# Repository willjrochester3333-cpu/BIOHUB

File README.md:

# Biohub — Cell Tracking During Development

Baseline solution for the Kaggle "Biohub - Cell Tracking During Development"
competition: detect zebrafish cells in 3D+time microscopy volumes, link them
across frames, recover cell divisions, and reconstruct lineages.

## Approach

No trained model or ground truth is required — this is a classical
computer-vision baseline meant to run standalone in a Kaggle Notebook with
internet access disabled, and to serve as a starting point to improve on.

1. **Detection** (`src/detection.py`): anisotropic Gaussian smoothing (voxel
   sigma derived from the physical scale, since z spacing is ~4x coarser
   than xy) → Otsu/relative intensity threshold → local maxima spaced by a
   physical radius (not voxel count) → marker-controlled watershed →
   intensity-weighted centroid per region.
2. **Linking** (`src/tracking.py`): frame-to-frame 1-1 assignment via the
   Hungarian algorithm (`scipy.optimize.linear_sum_assignment`) on
   physically-scaled centroid distance. The cost matrix is padded with
   dummy rows/columns (cost = distance threshold) so cells can appear,
   disappear, or go unmatched instead of being forced into a bad pairing.
3. **Division recovery**: any cell left unmatched by the 1-1 step is
   attached to its nearest neighbor in the previous frame (within a looser
   distance gate). If that parent already has an edge, it now has two —
   a division.
4. **Submission** (`src/submission.py`): formats nodes and edges into the
   required `submission.csv` schema.

## Layout

```
main.py          single-file version: everything inlined into one main()
notebook/kaggle_submission.ipynb   same thing, split across notebook cells
src/
  detection.py   3D blob detection for one timepoint volume
  tracking.py    frame-to-frame linking + division recovery
  data.py        zarr access (OME-NGFF multiscale, bare 4D/5D array, or legacy per-timepoint group)
  submission.py  submission.csv formatting
  pipeline.py    end-to-end driver (discovers test datasets, writes submission.csv)
notebook/
  kaggle_submission.ipynb   self-contained notebook to upload directly to Kaggle
tests/
  test_synthetic.py         smoke test on a synthetic moving+dividing cell
```

## Running

```bash
pip install -r requirements.txt
python3 -m pytest tests/ -v          # synthetic smoke test (no real data needed)
python3 -m src.pipeline              # edit TEST_DIR/OUTPUT_PATH at the bottom of pipeline.py

# or the single-file version (test_dir auto-detects a *.zarr folder under
# /kaggle/input if not given explicitly):
python3 main.py --output /kaggle/working/submission.csv
```

For the actual Kaggle submission, upload `notebook/kaggle_submission.ipynb`
as a Code Competition notebook, or paste the contents of `main.py` into a
single notebook cell and call:

```python
submission = main(output_path="/kaggle/working/submission.csv")
```

Both are fully self-contained (no dependency on this repo's `src/` package)
and produce byte-identical output — `main.py` is the same detect/link/divide/
submit logic as `src/`, just inlined into one `main()` function for people
who'd rather copy-paste one block than manage multiple files.
`discover_test_dir()` walks `/kaggle/input` looking for a folder that
directly contains `*.zarr` datasets (preferring one named `test`), since the
competition slug in the mounted path isn't known ahead of time — pass
`test_dir=...` explicitly to override.

`ZarrTimeSeries` (in `src/data.py`, `main.py`, and the notebook's data-access
cell) auto-detects the on-disk layout: OME-NGFF multiscale groups (using the
`.zattrs` `multiscales`/`axes` metadata to pick the finest resolution level
and the right time/channel axes), a bare `(T, Z, Y, X)` or `(T, C, Z, Y, X)`
array, or the legacy convention of one 3D array per timepoint keyed `"0"`,
`"1"`, .... If a real dataset doesn't fit any of these, run `inspect_zarr(path)`
(exported alongside `ZarrTimeSeries`) on it to print its structure and adjust
`ZarrTimeSeries._resolve` accordingly.

**Before relying on this for a leaderboard score**, tune `DetectionParams` /
`TrackingParams` against a few training volumes with known ground truth —
thresholds and distance gates are density- and noise-dependent.

## Where to improve

- Swap the classical watershed detector for a learned 3D segmentation model
  (e.g. StarDist3D or a U-Net), especially for dense/irregular cell
  populations where intensity-based watershed under- or over-segments.
- Add appearance features (intensity, size) to the linking cost, not just
  distance.
- Bridge missed detections with skip-frame linking (link t → t+2 when a
  cell has no match at t+1).
- Tighten division heuristics (`recover_divisions`) to cut false positives
  from detection noise — e.g. require daughter size/intensity symmetry.

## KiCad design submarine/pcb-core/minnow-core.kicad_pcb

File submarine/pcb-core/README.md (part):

# Minnow Core: the all-in-one board

This is the "buy almost nothing" version of the Minnow electronics. JLCPCB solders **every part** for you:
the ESP32, the USB programming port, the magnet on/off switch, the 5 V and 3.3 V supplies, the compass, the
hull leak/pressure sensor, the LoRa radio and all the connectors. There is nothing to solder on the board.

**The whole sub can be built without soldering.** Everything connects to the board with plugs (battery, camera,
antenna, USB) or **screw terminals** (strip a wire, push it in, tighten the screw), and the few wire-to-wire joins
use lever connectors and heat-shrink crimp splices. See [Building it without soldering](#building-it-without-soldering)
and the [solder-free shopping list](../bom/shopping_list.md).

**Order two.** One goes in the sub. The other is your **shore radio**: plug it into a laptop with a USB-C cable
and it talks to the sub over LoRa. You don't need any other radio, USB adapter or base station.

| Top | Bottom |
|---|---|
|  |  |

It has the same outline (150 x 60 mm) and mounting holes as the rev 1 carrier board in [`../pcb`](../pcb), so it
fits the same sled in the hull, and the mechanical design does not change. Two small differences: the magnet mark
moves to the side of the hull (see below), and because the board is lighter than the rev 1 board with its DevKit,
radio and compass bracket, the sub needs about 617 g of lead instead of 579 g (the 1 kg bag covers it). Build the
Blender model with `python3.11 build_sub.py --core` to see it and get the exact trim.

## What is on the board

| Job | Part on the board | Replaces (rev 1) |
|---|---|---|
| Brain | ESP32-WROOM-32E-N8 module (Wi-Fi for the camera, Bluetooth) | ESP32-S3 DevKit |
| Programming / shore link | USB-C + CH340C USB serial, auto-reset, BOOT and RESET buttons | DevKit USB, CH340 adapter |
| Compass / IMU | Bosch BNO055 9-axis sensor with its own sensor fusion, plus a 32.768 kHz crystal | BNO085 breakout |
| Hull monitor | Bosch BME280 (pressure for the vacuum test, humidity for early leak warning) | BME280 breakout |
| Radio | Ai-Thinker Ra-01H LoRa (SX1276, 868 MHz) with a U.FL antenna socket | 2 x E220 modules + USB adapter |
| On/off | Honeywell SM351LT magnet sensor at the board edge + always-on 3 uA supply: hold a magnet on the hull | reed switch on a lead |
| Power | 15 A fuse, two 40 A P-MOSFET switch, 18 V surge clamp, 5 V / 3 A buck (TPS54302), 3.3 V LDO | same idea, through-hole parts |
| Camera power | USB-A socket for the GoPro's own cable, switched by the ESP32, 1.5 A resettable fuse | USB-A breakout on a lead |
| Thrusters | Screw terminals for the signal wires of four single ESCs (DShot), 1 kΩ protection on every signal | JST-PH 7-pin to a 4-in-1 ESC |
| Outputs | Strobe and spare (lights / pump) low-side switches, up to 3 A each | same |
| Wiring | Screw terminals for the GPS, depth sensor, 2 leak probes, strobe and AUX (each screw labelled on the board); XT60 battery in, XT30 out to the ESCs | JST sockets |

```mermaid
flowchart LR
    BAT[3S battery XT60] --> F[15 A fuse] --> SW[2 x P-MOSFET switch]
    MAG((magnet)) -.-> HALL[SM351LT magnet sensor<br/>always on, 3 uA] --> SW
    SW --> ESCP[XT30 to the ESCs]
    SW --> BUCK[5 V / 3 A buck] --> LDO[3.3 V LDO]
    USB[USB-C] --> CH[CH340C] <--> MCU
    USB --> LDO
    LDO --> MCU[ESP32-WROOM-32E]
    MCU -- PWR_HOLD --> SW
    MCU -- I2C --> IMU[BNO055 compass] & BME[BME280 hull] & DEP[depth socket]
    MCU -- SPI --> LORA[Ra-01H LoRa] --> ANT[U.FL antenna]
    MCU -- UART --> GPS[GPS socket]
    MCU -- DShot x4 --> ESCS[ESC signal screw terminals]
    MCU --> CAM[camera USB-A 5 V] & OUT[strobe / AUX outputs]
    MCU -. Wi-Fi .-> GOPRO[GoPro]
```

## What you still need to buy

The board can't hold the things that must be outside the hull, at the top of the mast or under the
battery. These are the electronics you still buy (the mechanical parts are unchanged, see the
[shopping list](../bom/shopping_list.md)):

| Qty | Item | Why it can't be on the board | Link |
|---:|---|---|---|
| 1 | **GPS** Beitian BN-220 | needs to see the sky from the mast | [Amazon UK](https://www.amazon.co.uk/s?k=Beitian+BN-220+GPS) |
| 1 | **Depth sensor** MS5837-30BA module with the pins already fitted (+ female-to-male jumper wires) | must touch the water, through the rear cap | [Amazon UK](https://www.amazon.co.uk/s?k=MS5837-30BA) · [eBay UK](https://www.ebay.co.uk/sch/i.html?_nkw=MS5837-30BA) |
| 4 | **Single ESCs** (BLHeli_S / Bluejay, 20–30 A, DShot) **with their wires already attached** | they carry the motor current | [Amazon UK](https://www.amazon.co.uk/s?k=BLHeli_S+30A+ESC+2-4S+4+pack) |
| 4 | **Motors** A2212 1000KV | they are the thrusters | [Amazon UK](https://www.amazon.co.uk/s?k=A2212+1000KV+brushless+motor) |
| 1 | **Battery** 3S 18650 pack with BMS and XT60 | (+ charger) | [Amazon UK](https://www.amazon.co.uk/s?k=3S+18650+battery+pack+BMS+11.1V+XT60) |
| 1 | **GoPro** HERO5/6/7 Black + 64 GB card + short USB-A to USB-C cable | the 4K camera | [eBay UK](https://www.ebay.co.uk/sch/i.html?_nkw=GoPro+HERO5+Black) |
| 2 | **868 MHz antennas** with a U.FL plug: one with a ~30 cm cable for the mast, one for the shore board | the antenna must be above water | [Amazon UK](https://www.amazon.co.uk/s?k=868MHz+antenna+IPEX+u.fl) |
| 1 | **Small magnet** (6–10 mm neodymium disc) | it is the on/off key | [Amazon UK](https://www.amazon.co.uk/s?k=N52+neodymium+magnet+10mm+x+5mm) |
| 1 | **Wiring kit:** heat-shrink crimp splices (22–16 AWG), 2 Wago 221-415 lever connectors, an XT30 male lead | joins without solder | [splices](https://www.amazon.co.uk/s?k=heat+shrink+butt+connectors+waterproof+22-16+AWG) · [Wago](https://www.amazon.co.uk/s?k=Wago+221-415) · [XT30](https://www.amazon.co.uk/s?k=XT30+male+pigtail+14AWG) |
| 1 | Strobe: a **12 V white LED with wires attached** (built-in resistor) | it sits in the mast | [Amazon UK](https://www.amazon.co.uk/s?k=12V+white+LED+pre+wired) |

Compared with the rev 1 board this removes the ESP32 DevKit, the BNO085, the BME280, two E220 radios, the USB
serial adapter, the reed switch, the USB-A breakout, the 38 lines of loose PCB parts and all of the soldering.
The full list for the whole sub, with links, is the [solder-free shopping list](../bom/shopping_list.md).

## Cost

Rough numbers from JLCPCB's parts library on 2026-11-11 (check the live quote, prices move):

| | USD |
|---|---:|
| Parts for two boards (BNO055 $9, BME280 $8, Ra-01H $6.50 and ESP32 $4.60 each are most of it) | ~80 |
| "Extended part" loading fee, 19 kinds of part x $3 | ~57 |
| Assembly setup, stencil, machine soldering of the through-hole connectors and screw terminals | ~35 |
| 5 bare PCBs (2 get assembled, 3 spare) | ~10 |
| Shipping to the UK | ~15–30 |
| **Total before VAT** | **~200–215** |
| **With UK VAT (JLCPCB charges it at checkout)** | **about £190–205** |

The rev 1 parts it replaces (DevKit, PCB and its parts, BNO085, BME280, two E220 radios, USB adapter, reed switch,
USB-A breakout, antenna pigtails) come to about £80, so the Core board costs roughly £110–125 more. In exchange
there is no soldering, the board is assembled and inspected by machine, and you get a second board as the
shore station.

**Ways to bring it down:**
* Leave out the hull monitor U10 (BME280): mark it "do not place" on the BOM page. Saves about £17. The leak
  probes still work, and you lose the automatic vacuum test.
* (Not for a solder-free build: choosing **Economic** assembly and soldering the through-hole connectors and
  screw terminals yourself saves roughly £20–25.)

## Ordering from JLCPCB, step by step

1. Go to [jlcpcb.com/quote](https://cart.jlcpcb.com/quote) and upload
   [`output/minnow-core-gerbers.zip`](output/minnow-core-gerbers.zip). It reads 150 x 60 mm, 2 layers.
2. PCB options: thickness 1.6 mm, quantity 5, any colour, surface finish HASL lead-free (or ENIG). Leave
   everything else at the default.
3. Turn on **PCB Assembly**: **Standard** PCBA (needed for the three through-hole connectors), assemble the
   **top side**, PCBA quantity **2**. Leave "Confirm parts placement" on.
4. Upload [`output/minnow-core-jlcpcb-bom.csv`](output/minnow-core-jlcpcb-bom.csv) as the BOM and
   [`output/minnow-core-jlcpcb-cpl.csv`](output/minnow-core-jlcpcb-cpl.csv) as the CPL (pick-and-place) file.
5. On the parts page every line should match a part (they all carry an LCSC number). If a part shows
   "out of stock", pick the suggested alternative with the same package and value.
6. **Check the placement preview.** The CPL already includes the usual JLCPCB rotation fixes, but look at every
   chip: the dot or notch on the part must match the dot on the footprint, the electrolytic capacitors'
   stripe must be on the minus side, and the USB and XT connectors and the screw terminals (wire openings) must face
   the board edge. Rotate any that
   are wrong right there on the page. JLCPCB's engineers check it again before they build.
7. Pay. Boards usually arrive in about 1–2 weeks.

## Connectors

| Ref | Silkscreen | Pins (1 → n) | Goes to |
|---|---|---|---|
| J1 | BATTERY | 1 −, 2 + (XT60 male) | battery (XT60 female) |
| J2 | ESC POWER | 1 −, 2 + (XT30 female) | XT30 lead → two Wago lever connectors → the four ESC power leads |
| J10 + J17 | G M1 M2 / M3 M4 (screws, starboard edge) | ground, then the four DShot signals | the ESCs' signal wires (and one ground) |
| J5 + J15 | 5V G / TX RX (screws, starboard edge) | +5 V, GND, TX from the GPS, RX to the GPS | BN-220 GPS |
| J6 + J16 | 3V3 G / SDA SCL (screws, port edge) | +3.3 V, GND, I2C | MS5837-30BA depth sensor (address 0x76) |
| J8 / J9 | LF G / LR G (screws, port edge) | leak sense, GND | leak probes: two bare wire ends each, at the lowest point of the hull |
| J11 | S+ S- (screws, port edge) | +battery, switched − | 12 V strobe LED in the mast |
| J12 | A+ A- (screws, port edge) | +battery, switched − (up to 3 A, flyback diode fitted) | lights or a pump |
| J13 | CAMERA 5V | USB-A, 5 V switched, 1.5 A fuse | GoPro (its own USB cable) |
| J3 | USB | USB-C | laptop: programming, serial monitor, shore station |
| J4 | LORA ANT | U.FL | 868 MHz antenna |

**Screw terminals:** 3.5 mm pitch, they take wires from 28 AWG (thin GPS wires) to 16 AWG. Strip 5 mm, twist the
strands, push the wire in fully and tighten the screw with a 2.5 mm screwdriver. The label next to each screw on the
board says what goes there. Every ESC signal has a 1 kΩ resistor, so a wire in the wrong screw will not damage
the ESP32.

## Building it without soldering

| Join | How | Parts |
|---|---|---|
| Battery → board | XT60 plug | already on the battery |
| Board → 4 ESCs (power) | XT30 lead into ESC POWER; its red wire and the four ESC red wires go into one Wago 221-415, the black wires into the other | XT30 male lead, 2 Wago 221-415 |
| ESC signal wires → board | Screw terminals M1–M4, plus one ESC ground wire into G. If an ESC also has a red "BEC" wire, leave it unconnected and cover the end with heat-shrink | — |
| ESC motor wires → thruster cables (inside the hull) | Heat-shrink crimp butt splices: crimp, then shrink | 12 splices |
| Thruster cables → motors (in the water) | The same splices; the glue inside seals them. Add a second layer of adhesive heat-shrink over each | 12 splices |
| GPS → board | Cut the plug off the free end of its cable, strip the 4 wires, screw them in | — |
| Depth sensor → board | Female-to-male jumper wires onto its pins, the pin ends into the screw terminals | 4 jumper wires |
| Strobe | A 12 V LED with wires attached, straight into S+ / S- | — |
| Leak probes | Two stripped wire ends each, into LF / G and LR / G | thruster cable offcut |
| Camera, antennas, laptop | USB-A, U.FL and USB-C plugs | — |

Tools: a ratchet crimper for insulated terminals, a wire stripper, a heat gun (or a lighter) and a small
screwdriver. The 3D-printed parts need no heat-set inserts either: screws cut their own thread, and the nose ring
and tail cone use glued studs and nuts (see [the mechanical guide](../docs/01-mechanical.md#16-frame-fairings-and-fasteners)),
so no soldering iron or hot tip is used anywhere in the build.

## Switching it on and off: the magnet

The SM351LT magnet sensor (U2) sits right at the port (left) edge of the board, next to the white arrow
marked MAGNET on the silkscreen. In the hull that point is **on the left side of the hull, level with the
middle of the hull, 53 mm behind the centre of the middle clamp**. Put a sticker or paint mark there.

* **On:** hold the magnet against the mark for a second. The sensor needs only about 1 mT, which a 6–10 mm
  neodymium disc gives through the 4.3 mm pipe wall with plenty to spare. The green 5 V LED and the red status
  LED come on, and the firmware takes over the power switch.
* **Off:** hold the magnet there for 3 seconds. The strobe flashes, you take the magnet away, and it turns off.
* If it doesn't react, turn the magnet 90 degrees. This kind of sensor (magnetoresistive) responds to a field
  along the board, so a magnet held flat against the hull side is the right way.
* Off, the board draws about 3 µA (a 3 Ah pack would take decades to drain), but still disconnect the battery for
  storage and charge it outside the hull.

## ESP32 pin map

| GPIO | Signal | Notes |
|---:|---|---|
| 0 | `ESP_IO0` | BOOT button / auto-program |
| 1 | `ESP_TXD` | USB serial (CH340C) |
| 2 | `LED_STAT` | red status LED |
| 3 | `ESP_RXD` | USB serial (CH340C) |
| 4 | `LORA_DIO0` | LoRa interrupt |
| 5 | `LORA_NSS` | LoRa chip select |
| 12 | `AUX_EN` | AUX output (lights / pump) |
| 13 | `CAM_EN` | camera 5 V on |
| 14 | `STROBE_EN` | strobe output |
| 15 | `MAG_SENSE` | magnet sensor (low = magnet) |
| 16 | `GPS_TX` | UART2 RX <- GPS TX |
| 17 | `GPS_RX` | UART2 TX -> GPS RX |
| 18 | `LORA_SCK` | SPI |
| 19 | `LORA_MISO` | SPI |
| 21 | `SDA` | I2C |
| 22 | `SCL` | I2C |
| 23 | `LORA_MOSI` | SPI |
| 25 | `ESC_M2` | DShot motor 2 |
| 26 | `ESC_M3` | DShot motor 3 |
| 27 | `ESC_M4` | DShot motor 4 |
| 32 | `PWR_HOLD` | keeps the power switch on |
| 33 | `ESC_M1` | DShot motor 1 |
| 34 | `LEAK_F` | leak probe front (ADC1) |
| 35 | `LEAK_R` | leak probe rear (ADC1) |
| 36 | `VBAT_SENSE` | battery voltage x 22/122 (ADC1) |
| 39 | `ESC_CURR_F` | ESC current sensor (ADC1) |

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
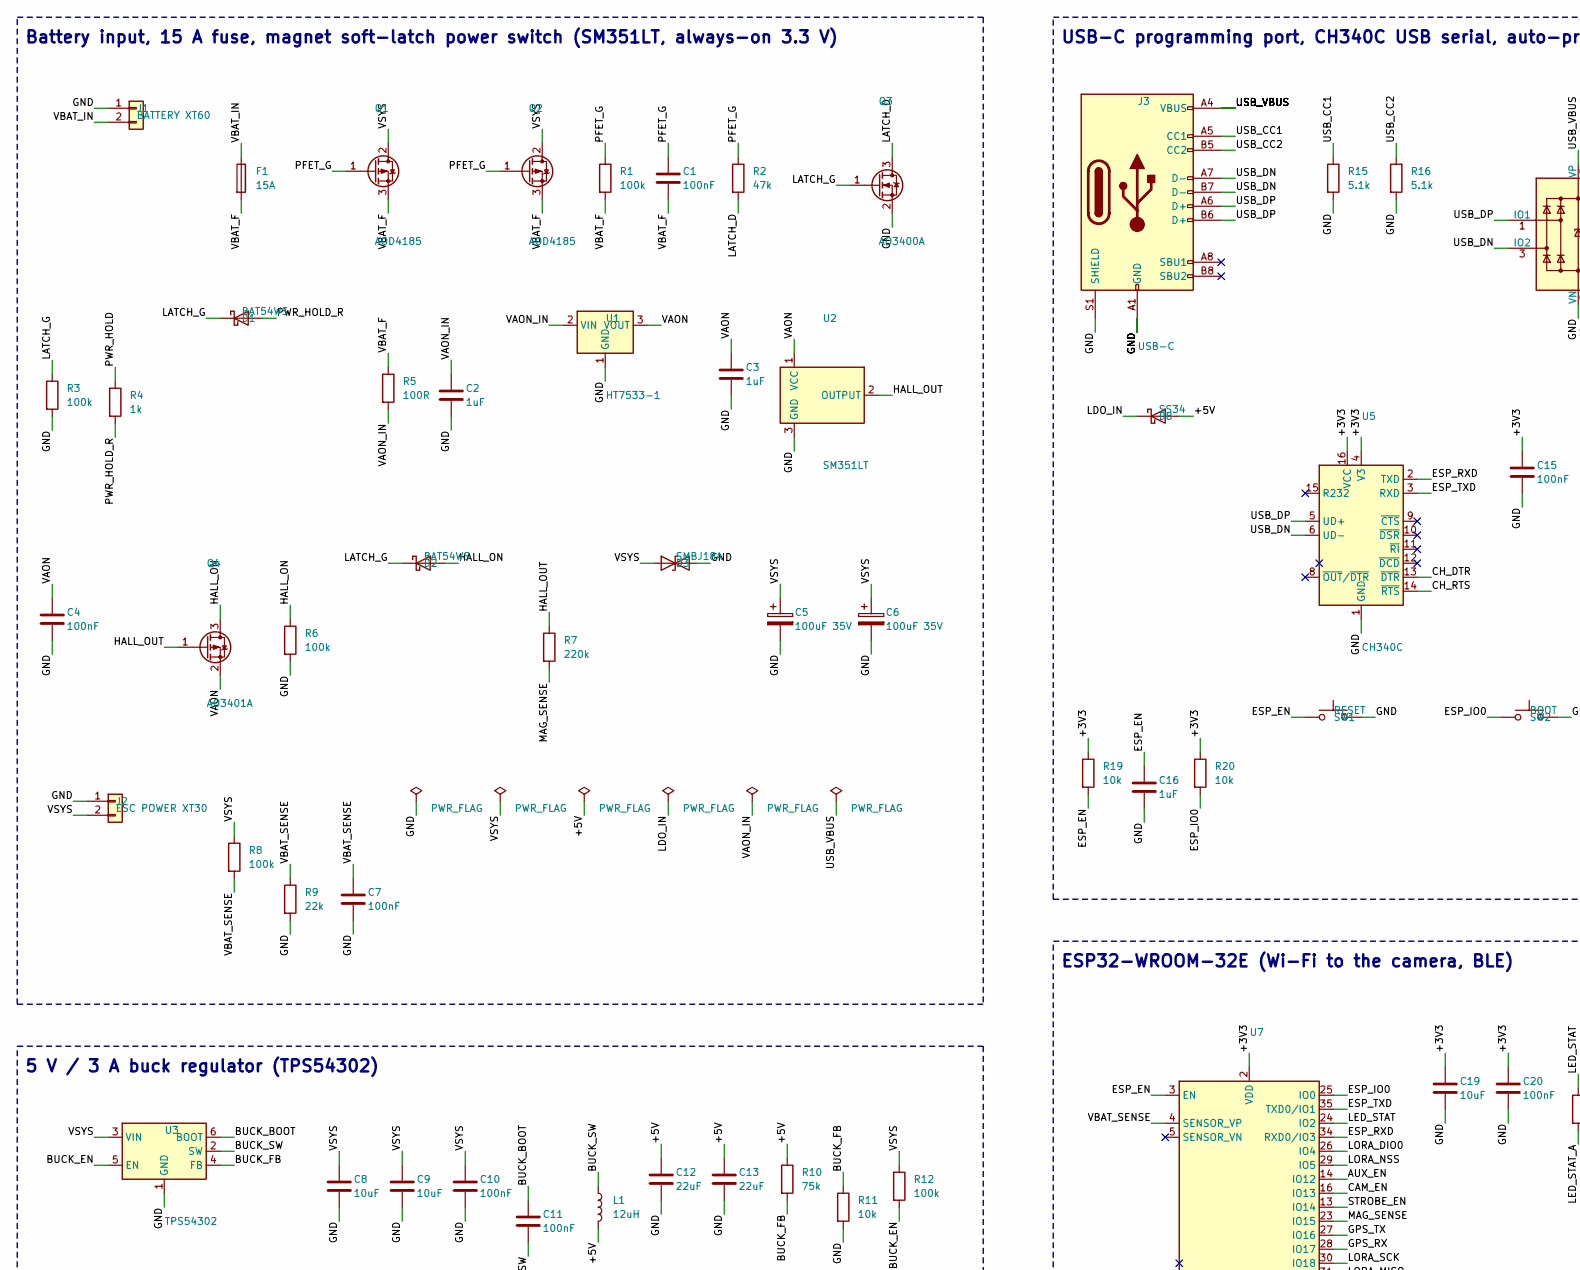
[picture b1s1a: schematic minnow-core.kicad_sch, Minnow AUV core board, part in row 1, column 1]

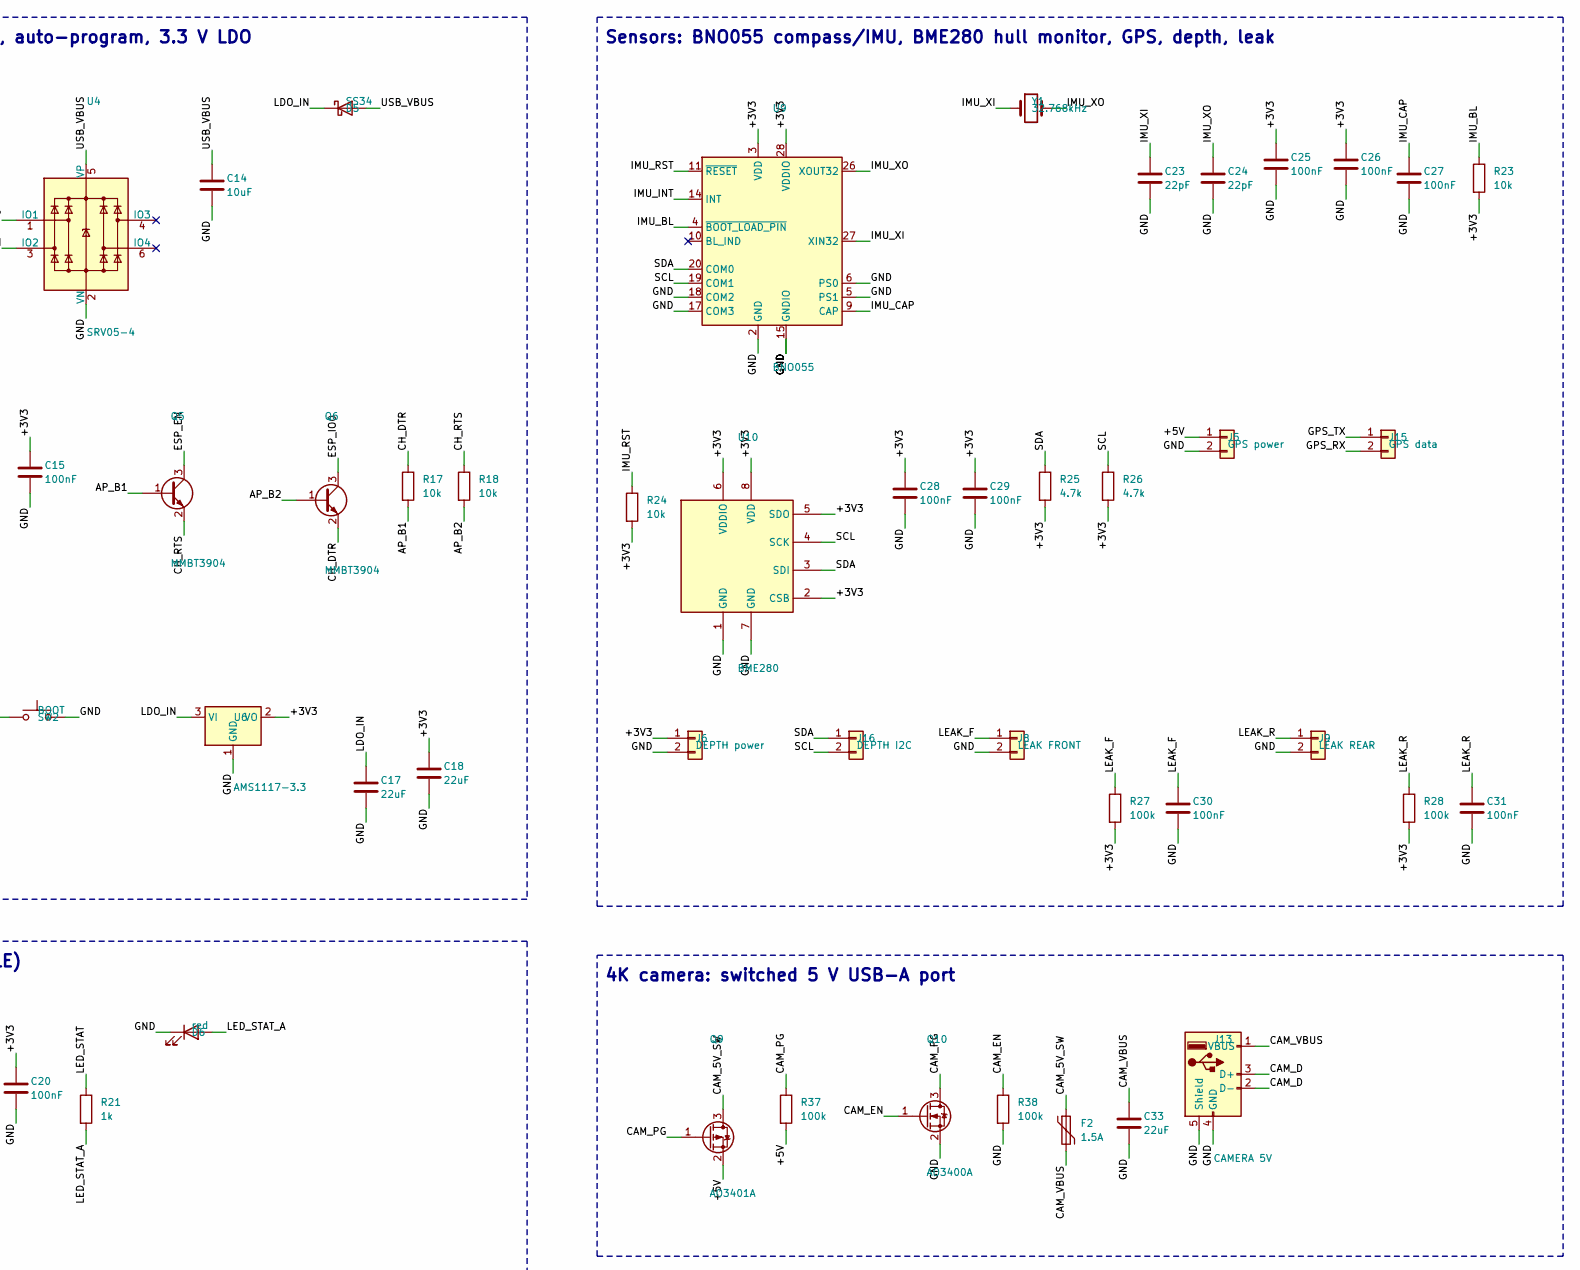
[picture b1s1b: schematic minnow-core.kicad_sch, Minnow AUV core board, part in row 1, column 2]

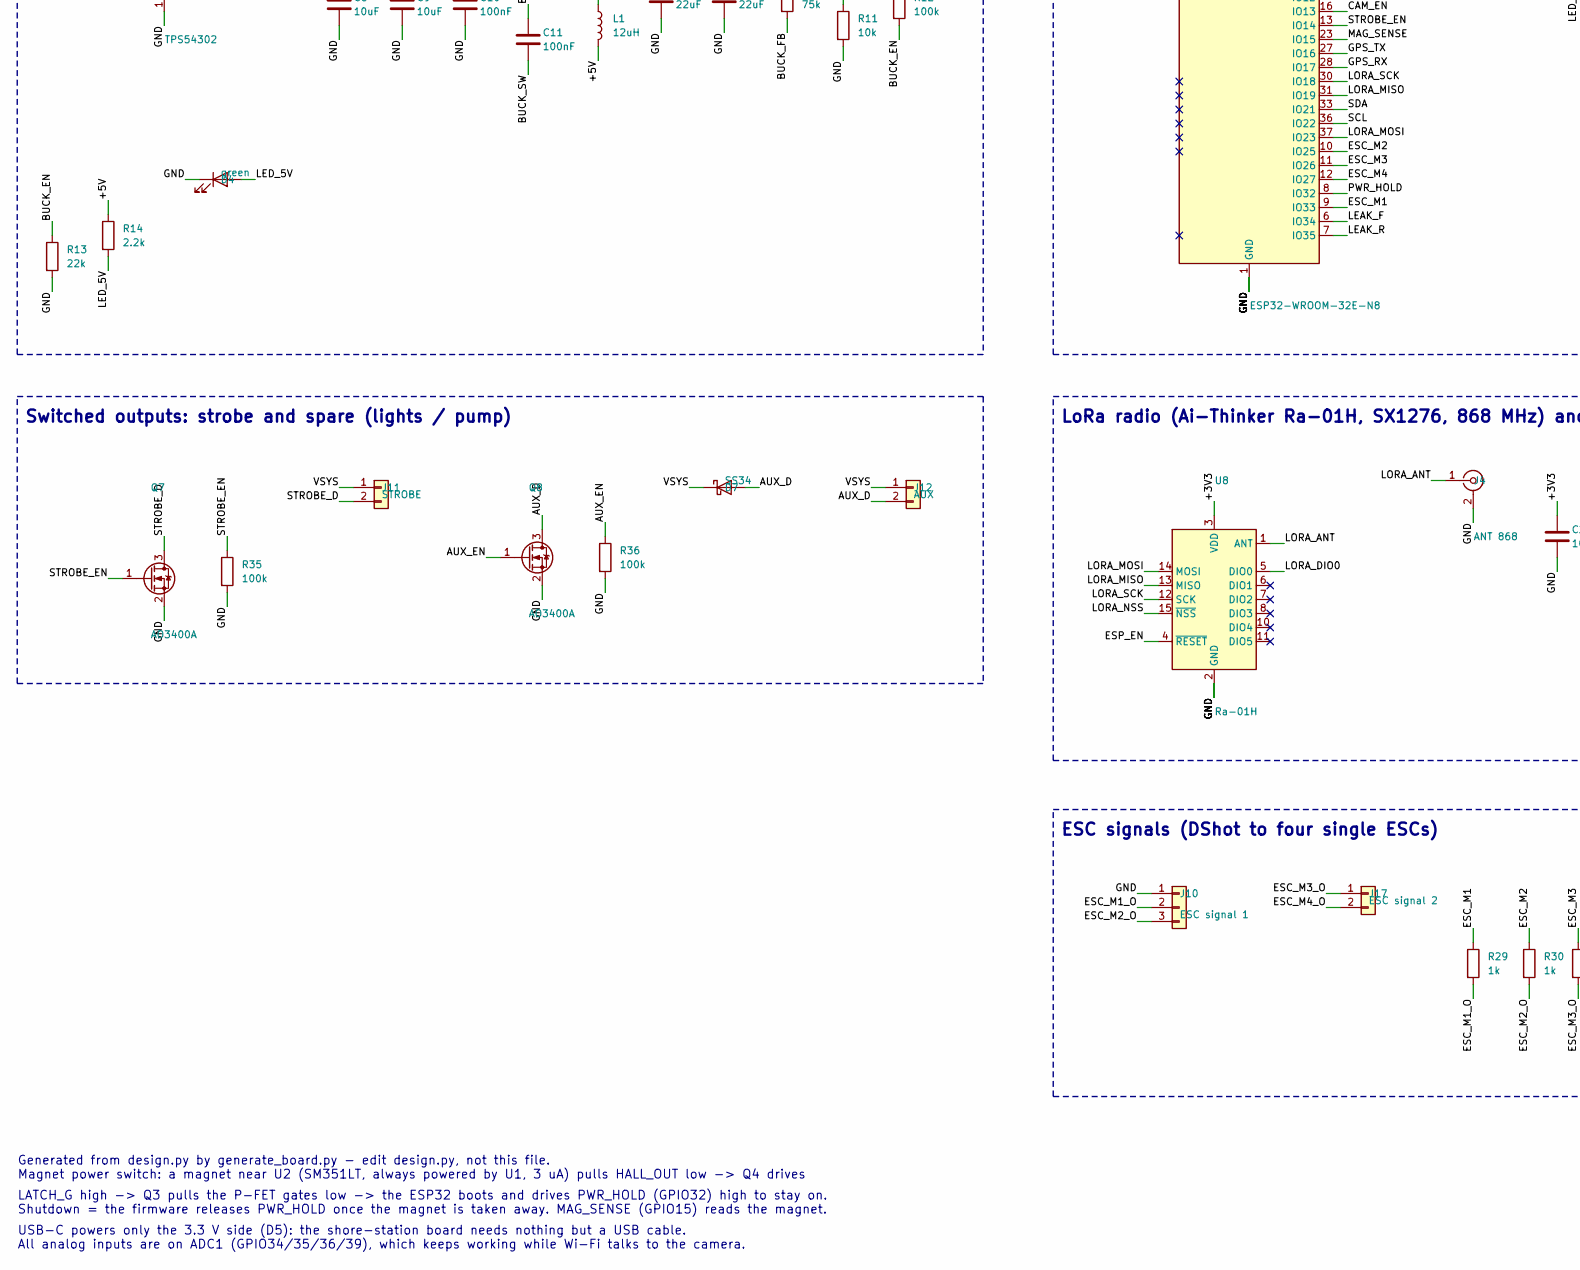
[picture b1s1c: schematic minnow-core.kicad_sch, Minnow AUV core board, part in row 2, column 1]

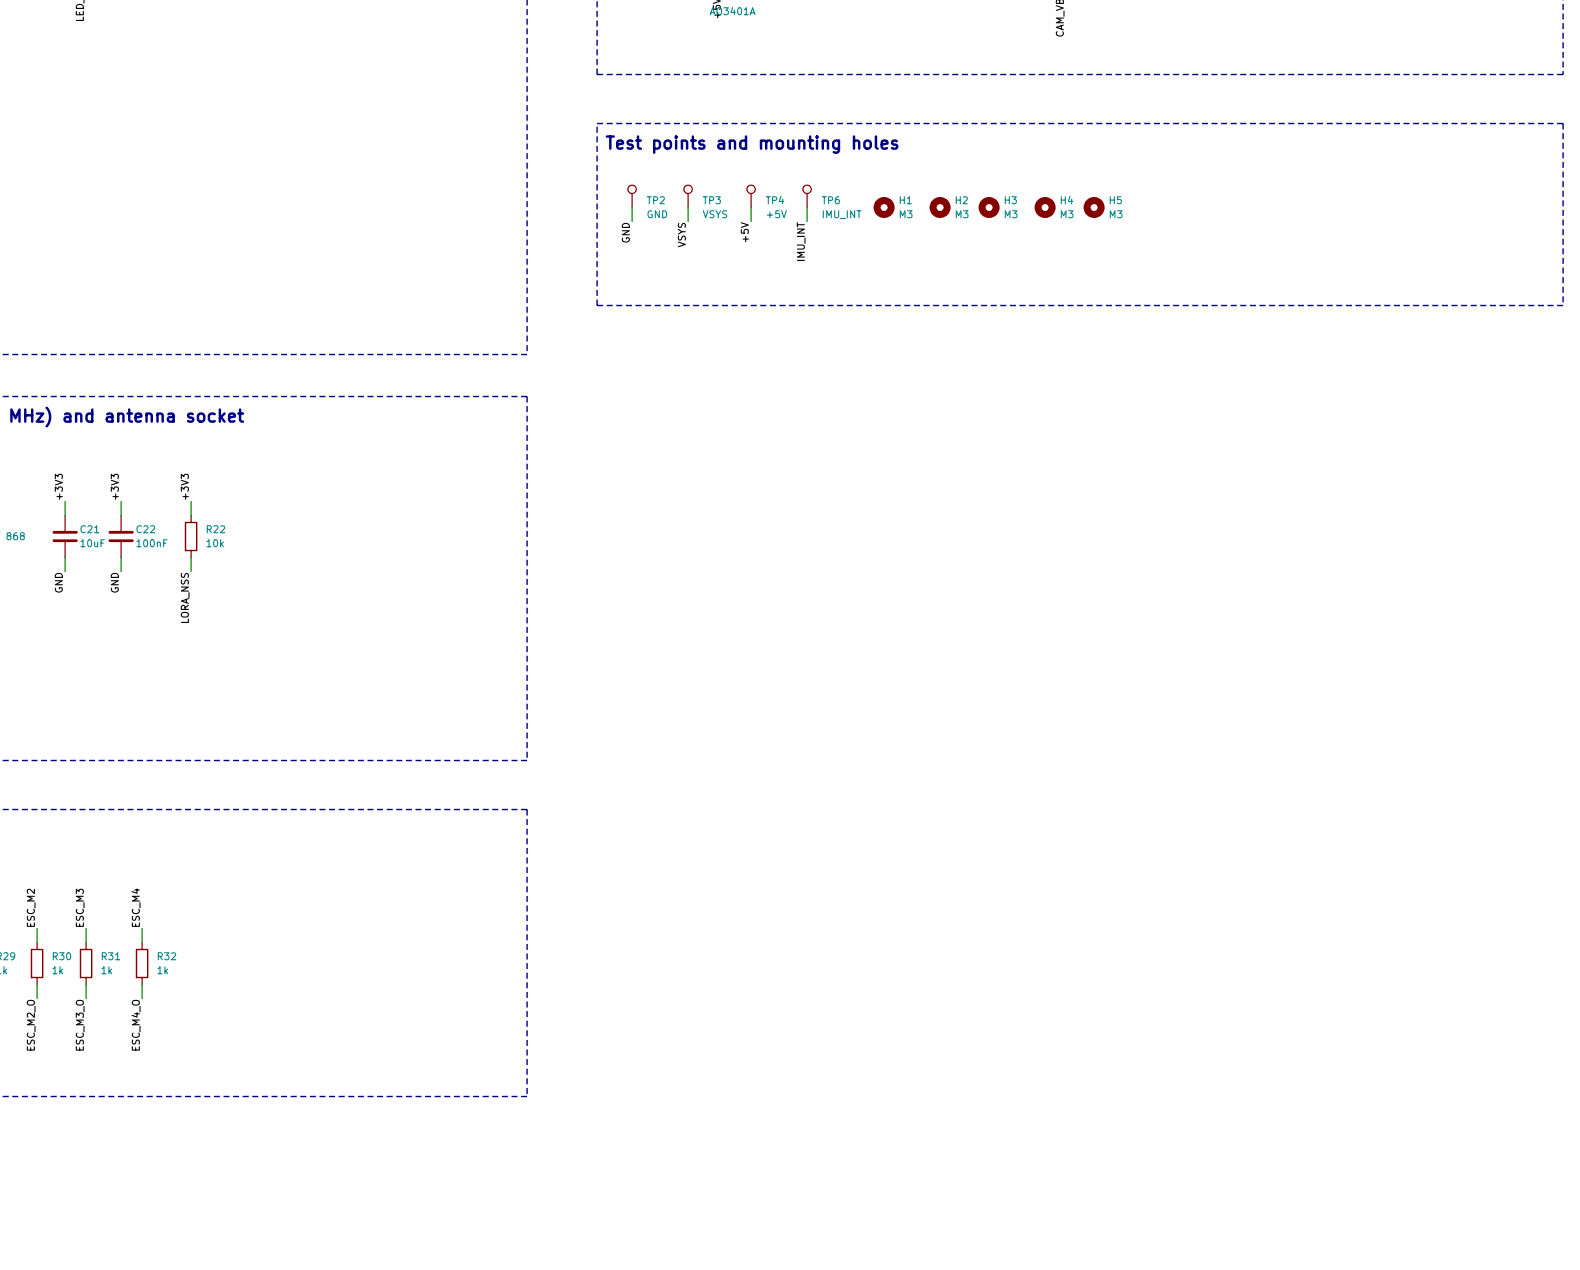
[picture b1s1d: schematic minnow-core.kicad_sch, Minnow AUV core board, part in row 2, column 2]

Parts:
C1: 100nF; C_0805_2012Metric; MPN 100 nF 50 V X7R 0805 (soft start)
C2, C3: 1uF; C_0805_2012Metric; MPN 1 uF 50 V X7R 0805
C4, C7, C10, C15, C20, C22, C28, C29, C30, C31: 100nF; C_0805_2012Metric; MPN 100 nF 50 V X7R 0805
C5, C6: 100uF 35V; CP_Elec_6.3x7.7; MPN 100 uF 35 V aluminium electrolytic, SMD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
C8, C9: 10uF; C_1206_3216Metric; MPN 10 uF X5R 1206 (50 V)
C11: 100nF; C_0805_2012Metric; MPN 100 nF 50 V X7R 0805 (bootstrap)
C12, C13, C17, C18, C33: 22uF; C_1206_3216Metric; MPN 22 uF 25 V X5R 1206
C14, C19, C21: 10uF; C_0805_2012Metric; MPN 10 uF X5R 0805
C16: 1uF; C_0805_2012Metric; MPN 1 uF 50 V X7R 0805 (reset delay)
C23, C24: 22pF; C_0805_2012Metric; MPN 22 pF 50 V C0G 0805
C25: 100nF; C_0805_2012Metric; MPN 100 nF 50 V X7R 0805 (VDD)
C26: 100nF; C_0805_2012Metric; MPN 100 nF 50 V X7R 0805 (VDDIO)
C27: 100nF; C_0805_2012Metric; MPN 100 nF 50 V X7R 0805 (BNO055 CAP pin)
D1, D2: BAT54WS; D_SOD-323; MPN BAT54WS Schottky SOD-323
D3: SMBJ18A; D_SMB; MPN SMBJ18A unidirectional TVS (ESC spikes)
D4: green; LED_0805_2012Metric; MPN green LED 0805 (5 V on)
D5: SS34; D_SMA; MPN SS34 3 A Schottky, SMA (USB powers only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
D6: red; LED_0805_2012Metric; MPN red LED 0805 (status)
D7: SS34; D_SMA; MPN SS34 flyback diode (pumps, motors)
D8: SS34; D_SMA; MPN SS34 3 A Schottky, SMA (5 V -> 3.3 V re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
F1: 15A; Fuse_1206_3216Metric; MPN JFC1206-2150FS 15 A 32 V fast fuse, 1206
F2: 1.5A; Fuse_1812_4532Metric; MPN 1812L150 resettable fuse 1.5 A hold
H1, H2, H3, H4, H5: M3; MountingHole_3.2mm_M3; MPN M3 mounting hole
J1: BATTERY XT60; AMASS_XT60PW-M_1x02_P7.20mm_Horizontal; MPN AMASS XT60PW-M (male, PCB, right angle)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
J2: ESC POWER XT30; AMASS_XT30UPB-F_1x02_P5.0mm_Vertical; MPN AMASS XT30UPB-F (female, PCB, vertical)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
J3: USB-C; USB_C_Receptacle_HRO_TYPE-C-31-M-12; MPN Korean Hroparts TYPE-C-31-M-12 USB-C re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
J4: ANT 868; U.FL_Hirose_U.FL-R-SMT-1_Vertical; MPN Hirose U.FL-R-SMT-1(80) antenna socket
J5: GPS power; TerminalBlock_Phoenix_PT-1,5-2-3.5-H_1x02_P3.50mm_Horizontal; MPN 2-way screw terminal, 3.5 mm pitch, 16-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
J6: DEPTH power; TerminalBlock_Phoenix_PT-1,5-2-3.5-H_1x02_P3.50mm_Horizontal; MPN 2-way screw terminal, 3.5 mm pitch, 16-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
J8: LEAK FRONT; TerminalBlock_Phoenix_PT-1,5-2-3.5-H_1x02_P3.50mm_Horizontal; MPN 2-way screw terminal, 3.5 mm pitch, 16-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
J9: LEAK REAR; TerminalBlock_Phoenix_PT-1,5-2-3.5-H_1x02_P3.50mm_Horizontal; MPN 2-way screw terminal, 3.5 mm pitch, 16-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
J10: ESC signal 1; TerminalBlock_Phoenix_PT-1,5-3-3.5-H_1x03_P3.50mm_Horizontal; MPN 3-way screw terminal, 3.5 mm pitch, 16-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
J11: STROBE; TerminalBlock_Phoenix_PT-1,5-2-3.5-H_1x02_P3.50mm_Horizontal; MPN 2-way screw terminal, 3.5 mm pitch, 16-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
J12: AUX; TerminalBlock_Phoenix_PT-1,5-2-3.5-H_1x02_P3.50mm_Horizontal; MPN 2-way screw terminal, 3.5 mm pitch, 16-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
J13: CAMERA 5V; USB_A_Molex_67643_Horizontal; MPN Molex 67643 USB-A socket (D+ joined to 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
J15: GPS data; TerminalBlock_Phoenix_PT-1,5-2-3.5-H_1x02_P3.50mm_Horizontal; MPN 2-way screw terminal, 3.5 mm pitch, 16-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
J16: DEPTH I2C; TerminalBlock_Phoenix_PT-1,5-2-3.5-H_1x02_P3.50mm_Horizontal; MPN 2-way screw terminal, 3.5 mm pitch, 16-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
J17: ESC signal 2; TerminalBlock_Phoenix_PT-1,5-2-3.5-H_1x02_P3.50mm_Horizontal; MPN 2-way screw terminal, 3.5 mm pitch, 16-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
L1: 12uH; L_Bourns_SRR1260; MPN Bourns SRR1260-120M 12 uH 5 A shielded
Q1: AOD4185; TO-252-2; MPN AOD4185 P-MOSFET -40 V -40 A DPAK
Q2: AOD4185; TO-252-2; MPN AOD4185 P-MOSFET -40 V -40 A DPAK (in p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
Q3, Q7, Q8, Q10: AO3400A; SOT-23; MPN AO3400A N-MOSFET 30 V 5.7 A SOT-23
Q4, Q9: AO3401A; SOT-23; MPN AO3401A P-MOSFET -30 V -4 A SOT-23
Q5: MMBT3904; SOT-23; MPN MMBT3904 NPN SOT-23 (auto-reset)
Q6: MMBT3904; SOT-23; MPN MMBT3904 NPN SOT-23 (auto-boot)
R1: 100k; R_0805_2012Metric; MPN 100k 0805 1% (gate pull-up: FETs off)
R2: 47k; R_0805_2012Metric; MPN 47k 0805 1% (gate divider: Vgs = 68 % o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
R3, R6, R27, R28, R35, R37, R38: 100k; R_0805_2012Metric; MPN 100k 0805 1%
R4, R21, R30, R31, R32: 1k; R_0805_2012Metric; MPN 1k 0805 1%
R5: 100R; R_0805_2012Metric; MPN 100R 0805 1% (spike filter)
R7: 220k; R_0805_2012Metric; MPN 220k 0805 1% (magnet state to the ESP32)
R8: 100k; R_0805_2012Metric; MPN 100k 0805 1% (battery divider top)
R9: 22k; R_0805_2012Metric; MPN 22k 0805 1% (battery divider bottom)
R10: 75k; R_0805_2012Metric; MPN 75k 0805 1% (Vout = 0.596 x (1 + 75/10)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
R11, R17, R18, R19, R20, R22, R24: 10k; R_0805_2012Metric; MPN 10k 0805 1%
R12: 100k; R_0805_2012Metric; MPN 100k 0805 1% (starts at 6.6 V)
R13: 22k; R_0805_2012Metric; MPN 22k 0805 1%
R14: 2.2k; R_0805_2012Metric; MPN 2.2k 0805 1%
R15, R16: 5.1k; R_0805_2012Metric; MPN 5.1k 0805 1% (USB-C sink)
R23: 10k; R_0805_2012Metric; MPN 10k 0805 1% (boot-loader pin high = nor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
R25, R26: 4.7k; R_0805_2012Metric; MPN 4.7k 0805 1% (I2C pull-up)
R29: 1k; R_0805_2012Metric; MPN 1k 0805 1% (limits current if a wire is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
R36: 100k; R_0805_2012Metric; MPN 100k 0805 1% (also keeps IO12 low at re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
SW1: RESET; SW_Push_1P1T_XKB_TS-1187A; MPN XKB TS-1187A-B-A-B tact switch
SW2: BOOT; SW_Push_1P1T_XKB_TS-1187A; MPN XKB TS-1187A-B-A-B tact switch
TP2: GND; TestPoint_Pad_D1.5mm; MPN test pad
TP3: VSYS; TestPoint_Pad_D1.5mm; MPN test pad
TP4: +5V; TestPoint_Pad_D1.5mm; MPN test pad
TP6: IMU_INT; TestPoint_Pad_D1.5mm; MPN test pad
U1: HT7533-1; SOT-89-3; MPN HT7533-1 3.3 V LDO, 30 V in, 2.5 uA, SO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
U2: SM351LT; SOT-23; MPN Honeywell SM351LT magnetoresistive swit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
U3: TPS54302; SOT-23-6; MPN TI TPS54302DDCR 3 A 28 V synchronous bu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
U4: SRV05-4; SOT-23-6; MPN SRV05-4 USB ESD protection, SOT-23-6
U5: CH340C; SOIC-16_3.9x9.9mm_P1.27mm; MPN WCH CH340C USB-serial (no crystal), SOI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
U6: AMS1117-3.3; SOT-223-3_TabPin2; MPN AMS1117-3.3 1 A LDO, SOT-223
U7: ESP32-WROOM-32E-N8; ESP32-WROOM-32E; MPN Espressif ESP32-WROOM-32E-N8 (8 MB flas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
U8: Ra-01H; Ai-Thinker-Ra-01-LoRa; MPN Ai-Thinker Ra-01H (SX1276, 803-930 MHz,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
U9: BNO055; LGA-28_5.2x3.8mm_P0.5mm; MPN Bosch BNO055 9-axis orientation sensor,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
U10: BME280; Bosch_LGA-8_2.5x2.5mm_P0.65mm_ClockwisePinNumbering; MPN Bosch BME280 hull pressure / humidity /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
Y1: 32.768kHz; Crystal_SMD_3215-2Pin_3.2x1.5mm; MPN 32.768 kHz 12.5 pF crystal 3215 (better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

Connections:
+3V3: C15.1, C18.1, C19.1, C20.1, C21.1, C22.1, C25.1, C26.1, C28.1, C29.1, J6.1, R19.1, R20.1, R22.1, R23.2, R24.2, R25.2, R26.2, R27.2, R28.2, U5.4 (V3), U5.16 (VCC), U6.2 (VO), U7.2 (VDD), U8.3 (VDD), U9.3 (VDD), U9.28 (VDDIO), U10.2 (CSB), U10.5 (SDO), U10.6 (VDDIO), U10.8 (VDD)
+5V: C12.1, C13.1, D8.2 (A), J5.1, L1.2, Q9.2 (S), R10.1, R14.1, R37.2, TP4.1
AP_B1: Q5.1 (B), R17.2
AP_B2: Q6.1 (B), R18.2
AUX_D: D7.2 (A), J12.2, Q8.3 (D)
AUX_EN: Q8.1 (G), R36.1, U7.14 (IO12)
BUCK_BOOT: C11.1, U3.6 (BOOT)
BUCK_EN: R12.2, R13.1, U3.5 (EN)
BUCK_FB: R10.2, R11.1, U3.4 (FB)
BUCK_SW: C11.2, L1.1, U3.2 (SW)
CAM_5V_SW: F2.1, Q9.3 (D)
CAM_D: J13.2 (D-), J13.3 (D+)
CAM_EN: Q10.1 (G), R38.1, U7.16 (IO13)
CAM_PG: Q9.1 (G), Q10.3 (D), R37.1
CAM_VBUS: C33.1, F2.2, J13.1 (VBUS)
CH_DTR: Q6.2 (E), R17.1, U5.13 (~DTR)
CH_RTS: Q5.2 (E), R18.1, U5.14 (~RTS)
ESC_M1: R29.1, U7.9 (IO33)
ESC_M1_O: J10.2, R29.2
ESC_M2: R30.1, U7.10 (IO25)
ESC_M2_O: J10.3, R30.2
ESC_M3: R31.1, U7.11 (IO26)
ESC_M3_O: J17.1, R31.2
ESC_M4: R32.1, U7.12 (IO27)
ESC_M4_O: J17.2, R32.2
ESP_EN: C16.1, Q5.3 (C), R19.2, SW1.1, U7.3 (EN), U8.4 (~RESET)
ESP_IO0: Q6.3 (C), R20.2, SW2.1, U7.25 (IO0)
ESP_RXD: U5.2 (TXD), U7.34 (RXD0/IO3)
ESP_TXD: U5.3 (RXD), U7.35 (TXD0/IO1)
GND: C2.2, C3.2, C4.2, C5.2, C6.2, C7.2, C8.2, C9.2, C10.2, C12.2, C13.2, C14.2, C15.2, C16.2, C17.2, C18.2, C19.2, C20.2, C21.2, C22.2, C23.2, C24.2, C25.2, C26.2, C27.2, C28.2, C29.2, C30.2, C31.2, C33.2, D3.2 (A2), D4.1 (K), D6.1 (K), J1.1, J2.1, J3.A1 (GND), J3.A12 (GND), J3.B1 (GND), J3.B12 (GND), J3.S1 (SHIELD), J4.2 (Ext), J5.2, J6.2, J8.2, J9.2, J10.1, J13.4 (GND), J13.5 (Shield), Q3.2 (S), Q7.2 (S), Q8.2 (S), Q10.2 (S), R3.2, R6.2, R9.2, R11.2, R13.2, R15.2, R16.2, R35.2, R36.2, R38.2, SW1.2, SW2.2, TP2.1, U1.1 (GND), U2.3 (GND), U3.1 (GND), U4.2 (VN), U5.1 (GND), U6.1 (GND), U7.1 (GND), U7.15 (GND), U7.38 (GND), U7.39 (GND), U8.2 (GND), U8.9 (GND), U8.16 (GND), U9.2 (GND), U9.5 (PS1), U9.6 (PS0), U9.15 (GNDIO), U9.16 (GNDIO), U9.17 (COM3), U9.18 (COM2), U9.25 (GNDIO), U10.1 (GND), U10.7 (GND)
GPS_RX: J15.2, U7.28 (IO17)
GPS_TX: J15.1, U7.27 (IO16)
HALL_ON: D2.2 (A), Q4.3 (D), R6.1
HALL_OUT: Q4.1 (G), R7.1, U2.2 (OUTPUT)
IMU_BL: R23.1, U9.4 (~BOOT_LOAD_PIN)
IMU_CAP: C27.1, U9.9 (CAP)
IMU_INT: TP6.1, U9.14 (INT)
IMU_RST: R24.1, U9.11 (~RESET)
IMU_XI: C23.1, U9.27 (XIN32), Y1.1
IMU_XO: C24.1, U9.26 (XOUT32), Y1.2
LATCH_D: Q3.3 (D), R2.2
LATCH_G: D1.1 (K), D2.1 (K), Q3.1 (G), R3.1
LDO_IN: C17.1, D5.1 (K), D8.1 (K), U6.3 (VI)
LEAK_F: C30.1, J8.1, R27.1, U7.6 (IO34)
LEAK_R: C31.1, J9.1, R28.1, U7.7 (IO35)
LED_5V: D4.2 (A), R14.2
LED_STAT: R21.1, U7.24 (IO2)
LED_STAT_A: D6.2 (A), R21.2
LORA_ANT: J4.1 (In), U8.1 (ANT)
LORA_DIO0: U7.26 (IO4), U8.5 (DIO0)
LORA_MISO: U7.31 (IO19), U8.13 (MISO)
LORA_MOSI: U7.37 (IO23), U8.14 (MOSI)
LORA_NSS: R22.2, U7.29 (IO5), U8.15 (~NSS)
LORA_SCK: U7.30 (IO18), U8.12 (SCK)
MAG_SENSE: R7.2, U7.23 (IO15)
PFET_G: C1.1, Q1.1 (G), Q2.1 (G), R1.1, R2.1
PWR_HOLD: R4.1, U7.8 (IO32)
PWR_HOLD_R: D1.2 (A), R4.2
SCL: J16.2, R26.1, U7.36 (IO22), U9.19 (COM1), U10.4 (SCK)
SDA: J16.1, R25.1, U7.33 (IO21), U9.20 (COM0), U10.3 (SDI)
STROBE_D: J11.2, Q7.3 (D)
STROBE_EN: Q7.1 (G), R35.1, U7.13 (IO14)
USB_CC1: J3.A5 (CC1), R15.1
USB_CC2: J3.B5 (CC2), R16.1
USB_DN: J3.A7 (D-), J3.B7 (D-), U4.3 (IO2), U5.6 (UD-)
USB_DP: J3.A6 (D+), J3.B6 (D+), U4.1 (IO1), U5.5 (UD+)
USB_VBUS: C14.1, D5.2 (A), J3.A4 (VBUS), J3.A9 (VBUS), J3.B4 (VBUS), J3.B9 (VBUS), U4.5 (VP)
VAON: C3.1, C4.1, Q4.2 (S), U1.3 (VOUT), U2.1 (VCC)
VAON_IN: C2.1, R5.2, U1.2 (VIN)
VBAT_F: C1.2, F1.2, Q1.3 (S), Q2.3 (S), R1.2, R5.1
VBAT_IN: F1.1, J1.2
VBAT_SENSE: C7.1, R8.2, R9.1, U7.4 (SENSOR_VP)
VSYS: C5.1, C6.1, C8.1, C9.1, C10.1, D3.1 (A1), D7.1 (K), J2.2, J11.1, J12.1, Q1.2 (D), Q2.2 (D), R8.1, R12.1, TP3.1, U3.3 (VIN)

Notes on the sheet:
Battery input, 15 A fuse, magnet soft-latch power switch (SM351LT, always-on 3.3 V)
5 V / 3 A buck regulator (TPS54302)
Switched outputs: strobe and spare (lights / pump)
USB-C programming port, CH340C USB serial, auto-program, 3.3 V LDO
ESP32-WROOM-32E (Wi-Fi to the camera, BLE)
LoRa radio (Ai-Thinker Ra-01H, SX1276, 868 MHz) and antenna socket
ESC signals (DShot to four single ESCs)
Sensors: BNO055 compass/IMU, BME280 hull monitor, GPS, depth, leak
4K camera: switched 5 V USB-A port
Test points and mounting holes
Generated from design.py by generate_board.py - edit design.py, not this file.
Magnet power switch: a magnet near U2 (SM351LT, always powered by U1, 3 uA) pulls HALL_OUT low -> Q4 drives
LATCH_G high -> Q3 pulls the P-FET gates low -> the ESP32 boots and drives PWR_HOLD (GPIO32) high to stay on.
Shutdown = the firmware releases PWR_HOLD once the magnet is taken away. MAG_SENSE (GPIO15) reads the magnet.
USB-C powers only the 3.3 V side (D5): the shore-station board needs nothing but a USB cable.
All analog inputs are on ADC1 (GPIO34/35/36/39), which keeps working while Wi-Fi talks to the camera.

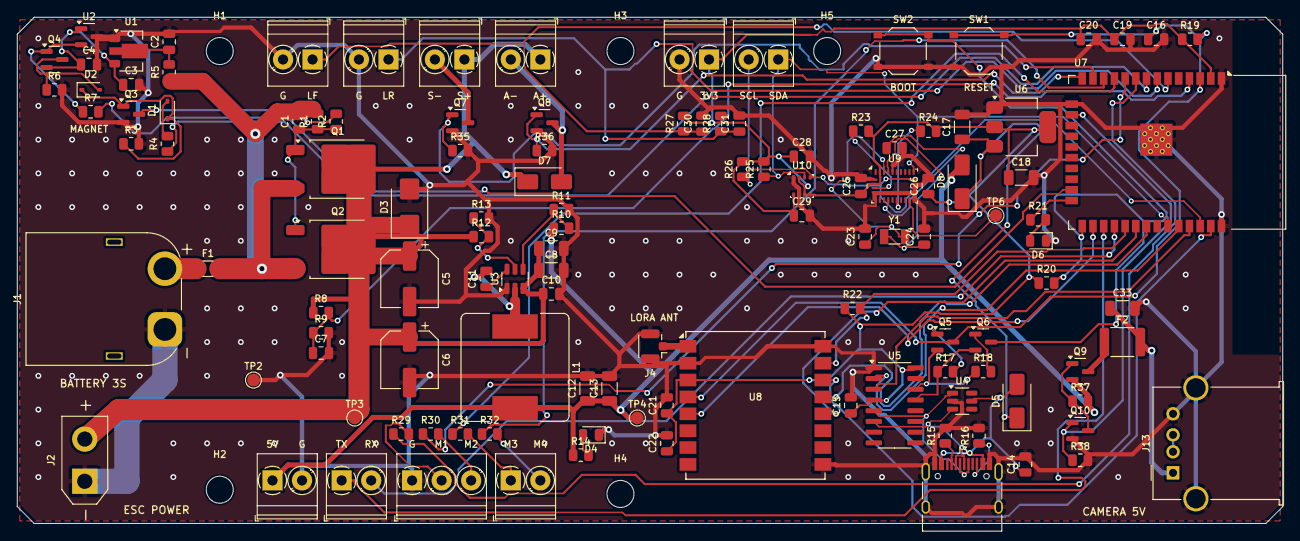
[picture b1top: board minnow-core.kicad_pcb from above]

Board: 2 copper layers, 150.0 x 60.0 mm, 126 parts (0 on the bottom side), 73 nets.

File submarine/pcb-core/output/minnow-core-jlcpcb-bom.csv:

Comment,Designator,Footprint,LCSC Part #,Description
100nF,"C1,C4,C7,C10,C11,C15,C20,C22,C25,C26,C27,C28,C29,C30,C31",C_0805_2012Metric,C49678,100 nF 50 V X7R 0805
1uF,"C2,C3,C16",C_0805_2012Metric,C28323,1 uF 50 V X7R 0805
100uF 35V,"C5,C6",CP_Elec_6.3x7.7,C72478,"100 uF 35 V aluminium electrolytic, SMD 6.3 x 7.7 mm"
10uF,"C8,C9",C_1206_3216Metric,C13585,10 uF X5R 1206
22uF,"C12,C13,C17,C18,C33",C_1206_3216Metric,C12891,22 uF 25 V X5R 1206
10uF,"C14,C19,C21",C_0805_2012Metric,C15850,10 uF X5R 0805
22pF,"C23,C24",C_0805_2012Metric,C1804,22 pF 50 V C0G 0805
BAT54WS,"D1,D2",D_SOD-323,C7502694,BAT54WS Schottky SOD-323
SMBJ18A,D3,D_SMB,C19077573,SMBJ18A unidirectional TVS (ESC spikes)
green,D4,LED_0805_2012Metric,C2297,green LED 0805 (5 V on)
SS34,"D5,D7,D8",D_SMA,C8678,"SS34 3 A Schottky, SMA"
red,D6,LED_0805_2012Metric,C84256,red LED 0805 (status)
15A,F1,Fuse_1206_3216Metric,C136356,"JFC1206-2150FS 15 A 32 V fast fuse, 1206"
1.5A,F2,Fuse_1812_4532Metric,C142805,1812L150 resettable fuse 1.5 A hold
BATTERY XT60,J1,AMASS_XT60PW-M_1x02_P7.20mm_Horizontal,C98732,"AMASS XT60PW-M (male, PCB, right angle) - through-hole"
ESC POWER XT30,J2,AMASS_XT30UPB-F_1x02_P5.0mm_Vertical,C108769,"AMASS XT30UPB-F (female, PCB, vertical) - through-hole"
USB-C,J3,USB_C_Receptacle_HRO_TYPE-C-31-M-12,C165948,Korean Hroparts TYPE-C-31-M-12 USB-C receptacle
ANT 868,J4,U.FL_Hirose_U.FL-R-SMT-1_Vertical,C88374,Hirose U.FL-R-SMT-1(80) antenna socket
GPS power / DEPTH power / LEAK FRONT / LEAK REAR / STROBE / AUX / GPS data / DEPTH I2C / ESC signal 2,"J5,J6,J8,J9,J11,J12,J15,J16,J17","TerminalBlock_Phoenix_PT-1,5-2-3.5-H_1x02_P3.50mm_Horizontal",C466970,"2-way screw terminal, 3.5 mm pitch, 16-28 AWG (DB125-3.5-2P) - through-hole"
ESC signal 1,J10,"TerminalBlock_Phoenix_PT-1,5-3-3.5-H_1x03_P3.50mm_Horizontal",C466971,"3-way screw terminal, 3.5 mm pitch, 16-28 AWG (DB125-3.5-3P) - through-hole"
CAMERA 5V,J13,USB_A_Molex_67643_Horizontal,C564920,"Molex 67643 USB-A socket (D+ joined to D- = ""charger"", so the camera may draw 1.5 A) - through-hole"
12uH,L1,L_Bourns_SRR1260,C1329355,Bourns SRR1260-120M 12 uH 5 A shielded
AOD4185,"Q1,Q2",TO-252-2,C400894,AOD4185 P-MOSFET -40 V -40 A DPAK
AO3400A,"Q3,Q7,Q8,Q10",SOT-23,C20917,AO3400A N-MOSFET 30 V 5.7 A SOT-23
AO3401A,"Q4,Q9",SOT-23,C15127,AO3401A P-MOSFET -30 V -4 A SOT-23
MMBT3904,"Q5,Q6",SOT-23,C20526,MMBT3904 NPN SOT-23
100k,"R1,R3,R6,R8,R12,R27,R28,R35,R36,R37,R38",R_0805_2012Metric,C149504,100k 0805 1%
47k,R2,R_0805_2012Metric,C17713,47k 0805 1% (gate divider: Vgs = 68 % of battery)
1k,"R4,R21,R29,R30,R31,R32",R_0805_2012Metric,C17513,1k 0805 1%
100R,R5,R_0805_2012Metric,C17408,100R 0805 1% (spike filter)
220k,R7,R_0805_2012Metric,C17556,220k 0805 1% (magnet state to the ESP32)
22k,"R9,R13",R_0805_2012Metric,C17560,22k 0805 1%
75k,R10,R_0805_2012Metric,C17819,75k 0805 1% (Vout = 0.596 x (1 + 75/10) = 5.07 V)
10k,"R11,R17,R18,R19,R20,R22,R23,R24",R_0805_2012Metric,C17414,10k 0805 1%
2.2k,R14,R_0805_2012Metric,C17520,2.2k 0805 1%
5.1k,"R15,R16",R_0805_2012Metric,C27834,5.1k 0805 1%
4.7k,"R25,R26",R_0805_2012Metric,C17673,4.7k 0805 1%
RESET / BOOT,"SW1,SW2",SW_Push_1P1T_XKB_TS-1187A,C318884,XKB TS-1187A-B-A-B tact switch
HT7533-1,U1,SOT-89-3,C14289,"HT7533-1 3.3 V LDO, 30 V in, 2.5 uA, SOT-89"
SM351LT,U2,SOT-23,C80830,"Honeywell SM351LT magnetoresistive switch, output low near a magnet, 0.36 uA"
TPS54302,U3,SOT-23-6,C311983,"TI TPS54302DDCR 3 A 28 V synchronous buck, SOT-23-6"
SRV05-4,U4,SOT-23-6,C85364,"SRV05-4 USB ESD protection, SOT-23-6"
CH340C,U5,SOIC-16_3.9x9.9mm_P1.27mm,C84681,"WCH CH340C USB-serial (no crystal), SOIC-16"
AMS1117-3.3,U6,SOT-223-3_TabPin2,C6186,"AMS1117-3.3 1 A LDO, SOT-223"
ESP32-WROOM-32E-N8,U7,ESP32-WROOM-32E,C701342,"Espressif ESP32-WROOM-32E-N8 (8 MB flash, PCB antenna)"
Ra-01H,U8,Ai-Thinker-Ra-01-LoRa,C503593,"Ai-Thinker Ra-01H (SX1276, 803-930 MHz, same pins as Ra-01); reset follows the ESP32 EN line"
BNO055,U9,LGA-28_5.2x3.8mm_P0.5mm,C93216,"Bosch BNO055 9-axis orientation sensor, I2C address 0x28 (PS0=PS1=COM3=0)"
BME280,U10,Bosch_LGA-8_2.5x2.5mm_P0.65mm_ClockwisePinNumbering,C92489,"Bosch BME280 hull pressure / humidity / temperature, I2C address 0x77 (SDO high)"
32.768kHz,Y1,Crystal_SMD_3215-2Pin_3.2x1.5mm,C32346,32.768 kHz 12.5 pF crystal 3215 (better compass timing)
